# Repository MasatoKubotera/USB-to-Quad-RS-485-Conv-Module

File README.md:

<html lang="en">

<head>
    <meta charset="uft-8">
    <meta name="author" content="Masato Kubotera">
    <meta name="description" content="">
</head>

<body>
    <p><strong>This product is currently under development!</strong></p>
    <h1>USB to Quad RS-485 Conv. Module</h1>
        <p>
            This product is USB to 4 RS-485 conversion module. The FTDI FT4232H is used for USB to quad UART conversion, and the Analog Devices ADM3078E is used for UART to RS-485 conversion. USB is 2.0 High Speed (480 Mb/s) and RS-485 supports a maximum baud rate of 16 MBps. The RS-485 I/O voltage is 3.3 V and is supplied by USB bus power from the regulator on the board. This product has a internal EEPROM and programmable in-circuit over USB using a utility program called FT_PROG available from FTDI’s web site (www.ftdichip.com). <br><br>
            Note: For this product, RI must be RS485 enabled (Enables the RI pin to be used as the TXDEN signal for RS485 busses) using FT_PROG in order to convert USB to RS-485 for transmission.
        </p>
    <h2>Features Rev. 1</h2>
        <p>
            <table>
                <tr>
                    <th>Top Surface of PCB</th>
                    <th>Bottom Surface of PCB</th>
                    <th>Assembled Electronic Components</th>
                </tr>
                <tr>
                    <td></td>
                    <td></td>
                    <td></td>
                </tr>
            </table>
        </p>
    <h3>PCB</h3>
        <p>
            <ul>
                <li>58 mm x 22.5 mm PCB layout</li>
                <li>
                    Two types of USB connectors
                    <ul>
                        <li>USB Mini-B Connector</li>
                        <li>1" (2.54mm) pitch through-holes for pin headers
                            <ul>
                                <li>VBUS</li>
                                <li>DM: USB Data Signal Minus</li>
                                <li>DP: USB Data Signal Plus</li>
                                <li>GND: Common Ground</li>
                            </ul>
                        </li>
                    </ul>
                </li>
                <li>
                    4 x RS-485 ports
                    <ul>
                        <li>1" (2.54mm) pitch through-holes for pin headers
                            <ul>
                                <li>3V3: 3.3 V power output (Power generated by the regulator on the board from USB bus power)</li>
                                <li>DP: RS-485 Data Signal Plus</li>
                                <li>DM: RS-485 Data Signal Minus</li>
                                <li>GND: Common Ground</li>
                            </ul>
                        </li>
                    </ul>
                </li>
                <li>
                    1 x Expansion port for FTDI FH4232HQ
                    <ul>
                        <li>1" (2.54mm) pitch through-holes for pin headers
                            <ul>
                                <li>3V3: 3.3 V power output (Power generated by the regulator on the board from USB bus power)</li>
                                <li>PWREN: Connected to FT4232HQ Pin#: 60 PWREN#</li>
                                <li>CLK: Connected to FT4232HQ Pin#: 62 EECLK</li>
                                <li>CS: Connected to FT4232HQ Pin#: 63 EECS</li>
                                <li>DATA: Connected to FT4232HQ Pin#: 61 EEDATA</li>
                                <li>GND: Common Ground</li>
                            </ul>
                    This port can be used for 4-channel transmit/receive LED display by decoding EEDATA data using 74HCT595, etc. Check the <a href="https://ftdichip.com/wp-content/uploads/2020/08/DS_FT4232H.pdf#page=33">Data Sheet</a> for details.
                        </li>
                    </ul>
                </li>
            </ul>
        </p>
    <h2>Development Environments</h2>
    <p>
        This product is designed with the following software.
            <ul>
                <li><a href="https://www.autodesk.com/products/eagle/overview">Autodesk Eagle 9.6.2</a></li>
            </ul>
    </p>
    <h2>Repository Contents</h2>
        <p>
            <dl>
                <dt><a href="/images">\images</a></dt>
                <dd>PCB preview images and capture of design screen</dd>
                <dt><a href="/libraries">\libraries</a></dt>
                <dd>Libraries used in Autodesk Eagle design</dd>
                <!--
                    <dt><a href="/documents">\documents</a> </dt>
                    <dd>Documentation for making and using this product</dd>
                -->
                <dt><a href="/pcb_order">\pcb_order</a> </dt>
                <dd>Gerber data and documentation for ordering PCB</dd>
                <dt><a href="/schematic.pdf">schematic.pdf</a></dt>
                <dd>Circuit diagram of this product</dd>
                <dt>*.brd</dt>
                <dd>Board wiring design file by Autodesk Eagle</dd>
                <dt>*.sch</dt>
                <dd>Circuit diagram design file by Autodesk Eagle</dd>
                <dt><a href="/.gitignore">.gitignore</a></dt>
                <dd>A file that tells Git not to track a particular file</dd>
                <dt><a href="/LICENSE">LICENSE</a></dt>
                <dd>License to use this product</dd>
            </dl>
        </p>
    <h2>Documentation</h2>
        <p>
            The following documents are available for this product.
            <ul>
                <li><a href="/pcb_order/README.md">\pcb_order\README.md</a>: Information for ordering the PCB</li>
            </ul>
        </p>
    <h2>References</h2>
        <p>
            This product was designed with reference to the following products.
            <ul>
                <li><a href="https://ftdichip.com/products/ft4232h-mini-module/">FTDI USB Hi-Speed FT4232H Evaluation Module: FT4232H Mini Module</a></li>
                <li><a href="https://kondo-robot.com/product/02133">KONDO RS485USB/Serial Conversion Adapter</a></li>
            </ul>
            In addition, the following documents were referenced in the design
            <ul>
                <li><a href="https://www.ftdichip.com/Support/Documents/AppNotes/AN_146_USB_Hardware_Design_Guidelines_for_FTDI_ICs.pdf">FTDI USB Hardware Design Guidelines for FTDI ICs</a></li>
                <li><a href="https://www.analog.com/media/en/analog-dialogue/volume-47/number-2/articles/safeguard-your-rs-485-communication-networks.pdf">Analog Devices Safeguard Your RS-485 Communication Networks from Harmful EMC Events</a></li>
                <li><a href="https://kondo-robot.com/w/wp-content/uploads/2014-B3M_series_manual_Ver.1.1.3.pdf#page=8">KONDO B3M Series Manual Ver1.13 pp.8</a></li>
            </ul>
        </p>
    <h2>Acknowledgements</h2>
        <p>
            The background to the development of this product was the development of QUADDXL, which was introduced in the following paper.
            <ul>
                <li>Bestmann, M., Güldenstein, J., Zhang, J. : High-Frequency Multi Bus Servo and Sensor Communication Using the Dynamixel Protocol. RoboCup 2019: Robot World Cup XXIII, pp.16–29 (2019)</li>
            </ul>
            Development data and other information on QUADDXL are available in the following repositories.
            <ul>
                <li><a href="https://github.com/bit-bots/bitbots_quaddxl">bit-bots/bitbots_quaddxl</a>: USB to RS485 Converter using FT4232H</li>
            </ul>
            I would like to take this opportunity to thank you.
        </p>
    <h2>Contact</h2>
        <p>
            If you have any questions, please contact the designer of this product, Masato Kubodera, by <a href="mailto:masato.kubotera@sustaina-op.com">e-mail</a>.<br>
            E-mail: <a href="mailto:masato.kubotera@sustaina-op.com">masato.kubotera@sustaina-op.com</a>
        </p>
    <h2>License Information</h2>
        <p>
            This product is open source. Please review the <a href="/LICENSE">LICENSE</a> for license information.<br>
            <br>
            This product by Masato Kubotera is licensed under a <a href="http://creativecommons.org/licenses/by-nc-sa/4.0/">Creative Commons Attribution-NonCommercial-ShareAlike 4.0 International License</a>.
        </p>
</body>
</html>

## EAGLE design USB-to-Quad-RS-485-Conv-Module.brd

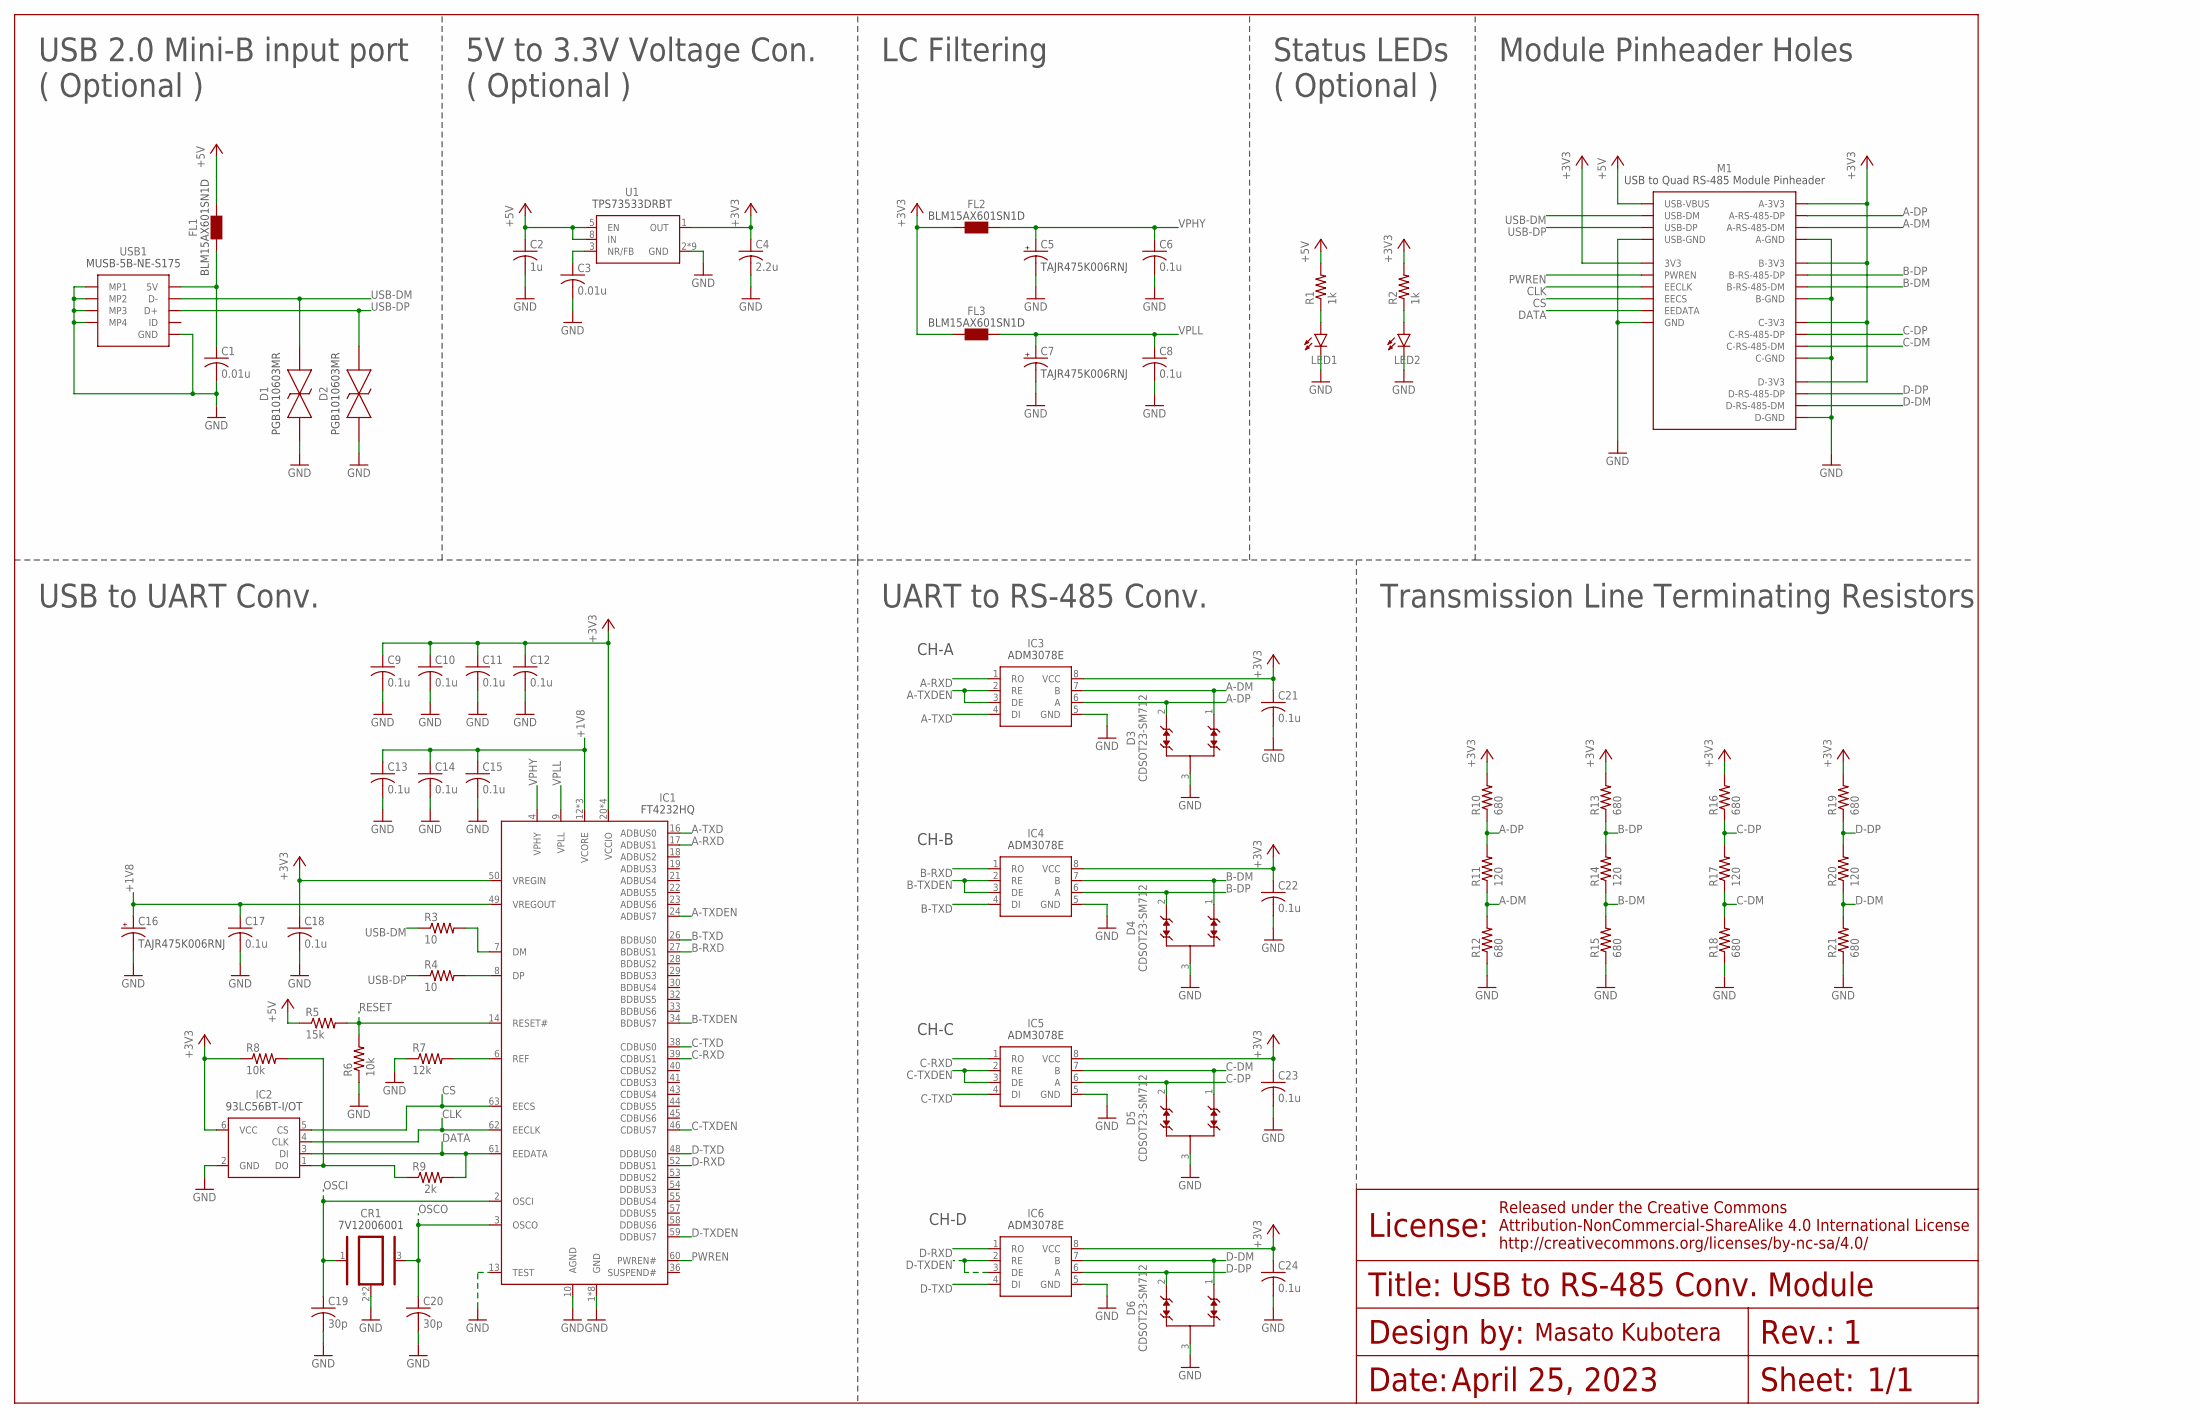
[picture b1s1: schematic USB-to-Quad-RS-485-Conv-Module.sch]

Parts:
C1, C3: 0.01u; C0402
C2: 1u; C0402
C4: 2.2u; C0402
C5, C7, C16: 4.7u; 0805K
C6, C8, C9, C10, C11, C12, C13, C14, C15, C17, C18, C21, C22, C23, C24: 0.1u; C0402
C19, C20: 30p; C0402
CR1: 7V12006001
D1, D2: PGB1010603MR; 0603
D3, D4, D5, D6: CDSOT23-SM712; SOT-23-3
FL1, FL2, FL3: BLM15AX601SN1D
IC1: FT4232HQ
IC2: 93LC56BT-I/OT; SOT-23-6
IC3, IC4, IC5, IC6: ADM3078E; SOIC-8
LED1, LED2: LEDSML0603; SML0603
M1: USB-TO-QUAD-RS-485-CONV-MODULE; USB-TO-QUAD-RS-485-CONV-MODULE-DIMENSION
R1, R2: 1k; R0402
R3, R4: 10; R0402
R5: 15k; R0402
R6, R8: 10k; R0402
R7: 12k; R0402
R9: 2k; R0402
R10, R12, R13, R15, R16, R18, R19, R21: 680; R0402
R11, R14, R17, R20: 120; R0402
U1: TPS73533DRBT; SON-8
USB1: MINI_USB_B_SMD

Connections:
+1V8: C13.1, C14.1, C15.1, C16.1 (+), C17.1, IC1.12 (VCORE), IC1.37 (VCORE), IC1.49 (VREGOUT), IC1.64 (VCORE)
+3V3: C4.1, C9.1, C10.1, C11.1, C12.1, C18.1, C21.1, C22.1, C23.1, C24.1, FL2.1, FL3.1, IC1.20 (VCCIO), IC1.31 (VCCIO), IC1.42 (VCCIO), IC1.50 (VREGIN), IC1.56 (VCCIO), IC2.6 (VCC), IC3.8 (VCC), IC4.8 (VCC), IC5.8 (VCC), IC6.8 (VCC), M1.3V3, M1.A-3V3, M1.B-3.3V (B-3V3), M1.C-3V3, M1.D-3V3, R2.2, R8.1, R10.2, R13.2, R16.2, R19.2, U1.1 (OUT)
+5V: C2.1, FL1.2, M1.USB-VBUS, R1.2, R5.1, U1.5 (EN), U1.8 (IN)
A-DM: D3.1, IC3.7 (B), M1.A-RS-485-DM, R11.1, R12.2
A-DP: D3.2, IC3.6 (A), M1.A-RS-485-DP, R10.1, R11.2
A-RXD: IC1.17 (ADBUS1), IC3.1 (RO)
A-TXD: IC1.16 (ADBUS0), IC3.4 (DI)
A-TXDEN: IC1.24 (ADBUS7), IC3.2 (RE), IC3.3 (DE)
B-DM: D4.1, IC4.7 (B), M1.B-RS-485-DM, R14.1, R15.2
B-DP: D4.2, IC4.6 (A), M1.B-RS-485-DP, R13.1, R14.2
B-RXD: IC1.27 (BDBUS1), IC4.1 (RO)
B-TXD: IC1.26 (BDBUS0), IC4.4 (DI)
B-TXDEN: IC1.34 (BDBUS7), IC4.2 (RE), IC4.3 (DE)
C-DM: D5.1, IC5.7 (B), M1.C-RS-485-DM, R17.1, R18.2
C-DP: D5.2, IC5.6 (A), M1.C-RS-485-DP, R16.1, R17.2
C-RXD: IC1.39 (CDBUS1), IC5.1 (RO)
C-TXD: IC1.38 (CDBUS0), IC5.4 (DI)
C-TXDEN: IC1.46 (CDBUS7), IC5.2 (RE), IC5.3 (DE)
CLK: IC1.62 (EECLK), IC2.4 (CLK), M1.EECLK
CS: IC1.63 (EECS), IC2.5 (CS), M1.EECS
D-DM: D6.1, IC6.7 (B), M1.D-RS-485-DM, R20.1, R21.2
D-DP: D6.2, IC6.6 (A), M1.D-RS-485-DP, R19.1, R20.2
D-RXD: IC1.52 (DDBUS1), IC6.1 (RO)
D-TXD: IC1.48 (DDBUS0), IC6.4 (DI)
D-TXDEN: IC1.59 (DDBUS7), IC6.2 (RE), IC6.3 (DE)
DATA: IC1.61 (EEDATA), IC2.3 (DI), M1.EEDATA, R9.2
FT4232H-DM: IC1.7 (DM), R3.2
FT4232H-DP: IC1.8 (DP), R4.2
FT4232H-REF: IC1.6 (REF), R7.2
GND: C1.2, C2.2, C3.2, C4.2, C5.2 (-), C6.2, C7.2 (-), C8.2, C9.2, C10.2, C11.2, C12.2, C13.2, C14.2, C15.2, C16.2 (-), C17.2, C18.2, C19.2, C20.2, C21.2, C22.2, C23.2, C24.2, CR1.2, CR1.4, D1.1, D2.1, D3.3, D4.3, D5.3, D6.3, IC1.1 (GND), IC1.5 (GND), IC1.10 (AGND), IC1.11 (GND), IC1.13 (TEST), IC1.15 (GND), IC1.25 (GND), IC1.35 (GND), IC1.47 (GND), IC1.51 (GND), IC2.2 (GND), IC3.5 (GND), IC4.5 (GND), IC5.5 (GND), IC6.5 (GND), LED1.C, LED2.C, M1.A-GND, M1.B-GND, M1.C-GND, M1.D-GND, M1.GND1 (GND), M1.USB-GND, R6.1, R7.1, R12.1, R15.1, R18.1, R21.1, U1.2 (GND), U1.4 (GND), U1.6 (GND), U1.7 (GND), U1.9 (GND), U1.10 (GND), U1.11 (GND), U1.12 (GND), U1.13 (GND), USB1.5 (GND), USB1.MP1, USB1.MP2, USB1.MP3, USB1.MP4
LED_3V3: LED2.A, R2.1
LED_5V: LED1.A, R1.1
NR/FB: C3.1, U1.3 (NR/FB)
OSCI: C19.1, CR1.1, IC1.2 (OSCI)
OSCO: C20.1, CR1.3, IC1.3 (OSCO)
PULLUP-DATA: IC2.1 (DO), R8.2, R9.1
PWREN: IC1.60 (PWREN#), M1.PWREN
RESET: IC1.14 (RESET#), R5.2, R6.2
USB-DM: D1.2, M1.USB-DM, R3.1, USB1.2 (D-)
USB-DP: D2.2, M1.USB-DP, R4.1, USB1.3 (D+)
VBUS: C1.1, FL1.1, USB1.1 (5V)
VPHY: C5.1 (+), C6.1, FL2.2, IC1.4 (VPHY)
VPLL: C7.1 (+), C8.1, FL3.2, IC1.9 (VPLL)

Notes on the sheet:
USB to UART Conv.
UART to RS-485 Conv.
CH-A
CH-D
CH-C
CH-B
Transmission Line Terminating Resistors
Module Pinheader Holes
Status LEDs ( Optional )
LC Filtering
5V to 3.3V Voltage Con. ( Optional )
USB 2.0 Mini-B input port ( Optional )
1/1
April 25, 2023
USB to RS-485 Conv. Module

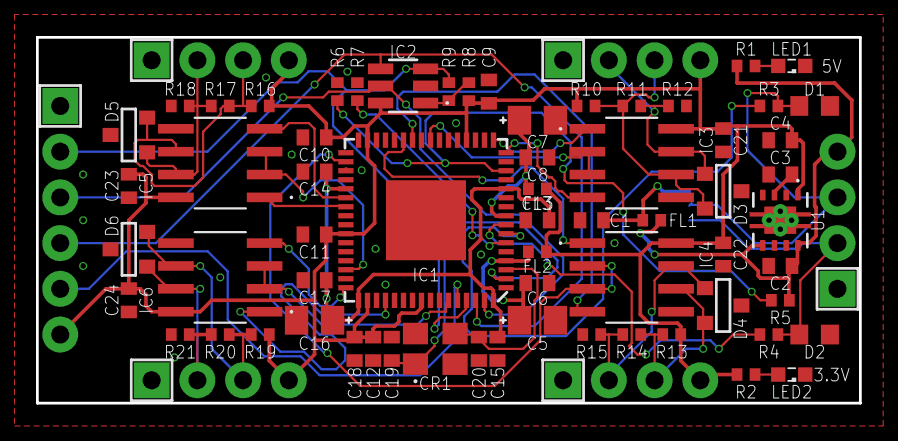
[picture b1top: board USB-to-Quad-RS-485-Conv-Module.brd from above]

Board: 2 copper layers, 45.7 x 20.3 mm, 66 parts (1 on the bottom side), 43 nets.

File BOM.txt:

Partlist exported from C:/Users/Masato/OneDrive - Chiba Institute of Technology/CIT Brains/RoboCup2023/USB-to-Quad-RS-485-Conv-Module/USB-to-Quad-RS-485-Conv-Module.sch at 2023/04/25 19:38

Qty Value                          Device                         Package                                  Parts                                                                  Description                
2                                  LEDSML0603                     SML0603                                  LED1, LED2                                                             LED                        
2   0.01u                          C-USC0402                      C0402                                    C1, C3                                                                 CAPACITOR, American symbol 
15  0.1u                           C-USC0402                      C0402                                    C6, C8, C9, C10, C11, C12, C13, C14, C15, C17, C18, C21, C22, C23, C24 CAPACITOR, American symbol 
2   10                             R-US_R0402                     R0402                                    R3, R4                                                                 RESISTOR, American symbol  
2   10k                            R-US_R0402                     R0402                                    R6, R8                                                                 RESISTOR, American symbol  
4   120                            R-US_R0402                     R0402                                    R11, R14, R17, R20                                                     RESISTOR, American symbol  
1   12k                            R-US_R0402                     R0402                                    R7                                                                     RESISTOR, American symbol  
1   15k                            R-US_R0402                     R0402                                    R5                                                                     RESISTOR, American symbol  
2   1k                             R-US_R0402                     R0402                                    R1, R2                                                                 RESISTOR, American symbol  
1   1u                             C-USC0402                      C0402                                    C2                                                                     CAPACITOR, American symbol 
1   2.2u                           C-USC0402                      C0402                                    C4                                                                     CAPACITOR, American symbol 
1   2k                             R-US_R0402                     R0402                                    R9                                                                     RESISTOR, American symbol  
2   30p                            C-USC0402                      C0402                                    C19, C20                                                               CAPACITOR, American symbol 
3   4.7u                           TAJR475K006RNJ                 0805K                                    C5, C7, C16                                                                                       
8   680                            R-US_R0402                     R0402                                    R10, R12, R13, R15, R16, R18, R19, R21                                 RESISTOR, American symbol  
1   7V12006001                     7V12006001                     7V12006001                               CR1                                                                                               
1   93LC56BT-I/OT                  93LC56BT-I/OT                  SOT-23-6                                 IC2                                                                                               
4   ADM3078E                       ADM3078E                       SOIC-8                                   IC3, IC4, IC5, IC6                                                                                
3   BLM15AX601SN1D                 BLM15AX601SN1D                 BLM15AX601SN1D                           FL1, FL2, FL3                                                                                     
4   CDSOT23-SM712                  CDSOT23-SM712                  SOT-23-3                                 D3, D4, D5, D6                                                                                    
1   FT4232HQ                       FT4232HQ                       FT4232HQ                                 IC1                                                                                               
1   MINI_USB_B_SMD                 MINI_USB_B_SMD                 MINI_USB_B_SMD                           USB1                                                                                              
2   PGB1010603MR                   PGB1010603MR                   0603                                     D1, D2                                                                                            
1   TPS73533DRBT                   TPS73533DRBT                   SON-8                                    U1                                                                                                
1   USB-TO-QUAD-RS-485-CONV-MODULE USB-TO-QUAD-RS-485-CONV-MODULE USB-TO-QUAD-RS-485-CONV-MODULE-DIMENSION M1

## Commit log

2023-04-26 Initial Upload

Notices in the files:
parts and their libraries:
Frames: Released under the Creative Commons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
